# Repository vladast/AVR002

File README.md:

# AVR-based event recorder with USB support

Event recorder device based on AVR processor, with the USB support enabled via V-USB library.

* **Project code name**: Fisherman's Friend
* **Homepage**: https://github.com/vladast/avr-based-event-recorder-with-usb-support

## Hardware

Key components of the hardware implementation are:
* **Atmel's Atmega8 processor**: a heart of the device, within which all logic lies.
* **ST's 24c64 EEPROM**: a persistent memory of the device.

Schematic diagram and PCB outline are created with Eagle v6 and can be found within **hw** directory.

## Software

Software part of the project consist of two parts:
* **Firmware**: a program being uploaded to device.
* **Test application**: a program running on host machine.

Programming languages used: C & C++.

Source code is located within **sw** directory.

## Configuration

There are couple of properties that have to be updated within Makefile before build can be started - following values should be set correctly:
* **PROGRAMMER**: By default, it states *rs232* which is the programmer used on test circuit. It should be set to the programmer's name from avrdude's configuration.
* **USB_CFG_VENDOR_ID**: USB VID 16bit value (see Makefile comments for more info, or refer to V-USB's site)
* **USB_CFG_DEVICE_ID**: USB PID 16bit value (see Makefile comments for more info, or refer to V-USB's site)
* **USB_CFG_VENDOR_NAME**: Name of the vendor. By default, for testing purposes, it's set to "TEST"
* **USB_CFG_VENDOR_NAME_LEN**: Number of chars within your vendor's name. For "TEST" string, that number is 4.
* **USB_CFG_DEVICE_NAME**: Name of your product. By default, for testing purposes, it's set to "TEST"
* **USB_CFG_DEVICE_NAME_LEN**: Number of chars within your vendor's name. For "TEST" string, that number is 4.

## Build procedure

At this moment, Makefile has only been intended for usage on Linux-based build machines with gcc and avr-gcc compilers installed. 
In general, with some modifications, it can be used on other platforms.

To build both firmware and test application run:

```
make build
```

To build only device's firmware (HEX file):

```
make build_hex
```

And to build only test application for host machine:

```
make build_test
```

To list all options from Makefile, run:

```
make
```

## Uploading firmware onto device

Used Makefile is configured for usage of *avrdude* programmer. To upload firmware to AVR located on device run:

```
make burn_firmware
```

**Note**: To use external crystal oscillator, for AVR chip used (which is Atmega8 at this moment), fuses has to be set first. To do so, run:

```
make burn_fuses
```

Of course, both of those commands should be issued as is from **sw** directory.

## 3rd party libraries

Following libraries were used:

* **V-USB**: A firmware-only USB driver for Atmel AVR Microcontrollers, enabling USB communication with host device. Library itself and documentation can be found on www.obdev.at/vusb/. 
V-USB is licensed under GPL version 2.
* **24C EEPROM SPI**: Enables easy SPI communication with external EEPROM. It's usage is well described on http://extremeelectronics.co.in/avr-tutorials/easy-24c-i2c-serial-eeprom-interfacing-with-avr-microcontrollers/

## Author and Licence

**avr-based-event-recorder-with-usb-support** repository is maintained by *Vladimir Stankovic*.

This project is licensed under *GPL Version 2*. Please, refer to LICENSE file for the full text of the license.

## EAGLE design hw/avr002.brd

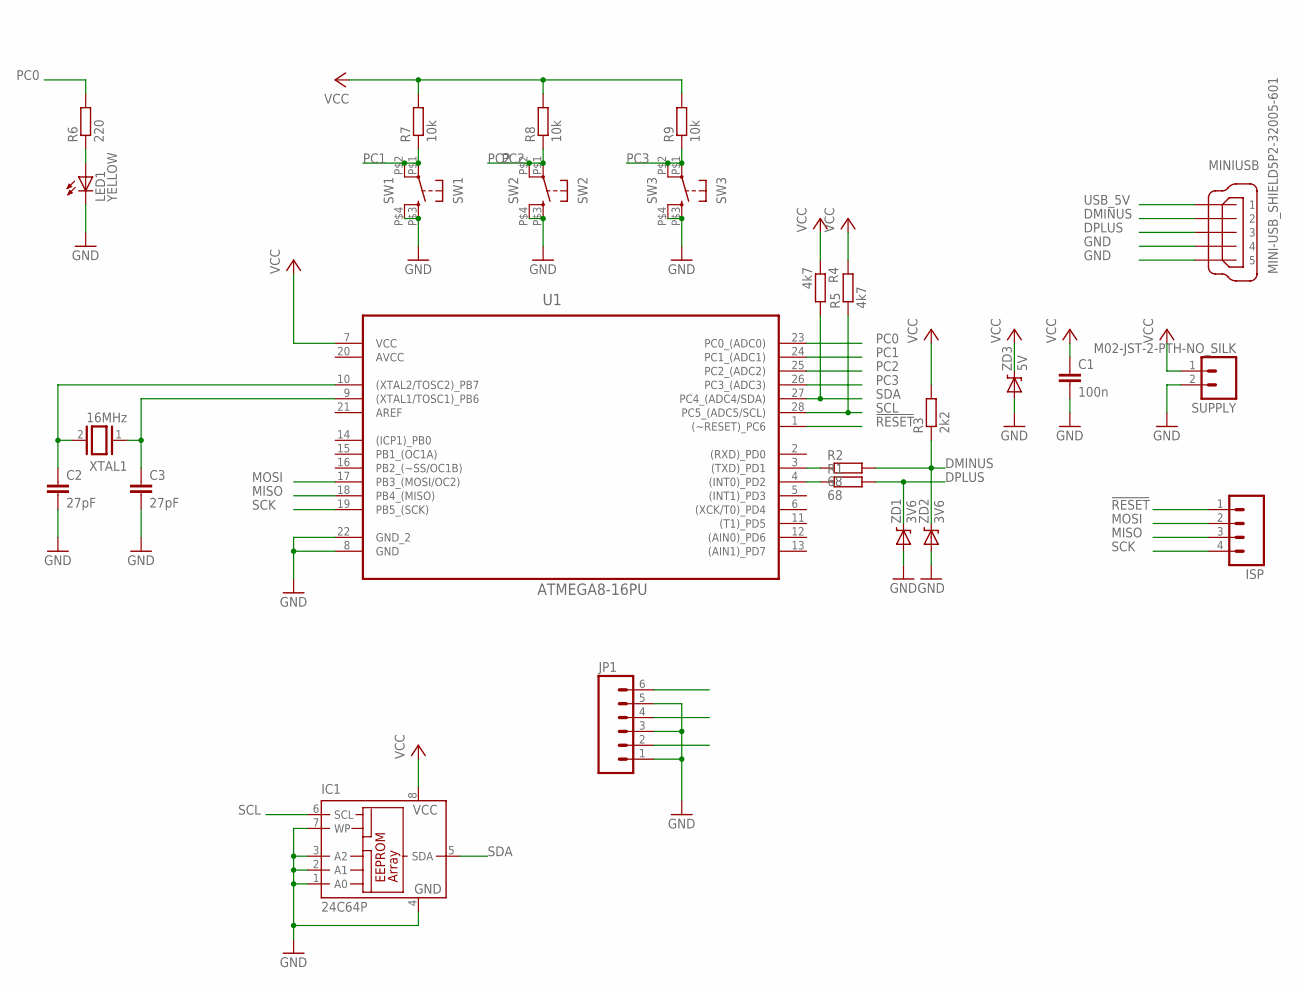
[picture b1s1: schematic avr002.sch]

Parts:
C1: 100n; C050-024X044
C2, C3: 27pF; C050-024X044
IC1: 24C64P; DIL8
ISP: M04POLAR; MOLEX-1X4
JP1: M06POLAR; MOLEX-1X6
LED1: YELLOW; LED5MM
MINIUSB: MINI-USB_SHIELD5P2-32005-601; 32005-601
R1, R2: 68; 0204/7
R3: 2k2; 0204/7
R4, R5: 4k7; 0204/7
R6: 220; 0204/7
R7, R8, R9: 10k; 0204/7
SUPPLY: M02-JST-2-PTH-NO_SILK; JST-2-PTH-NS
SW1: SW1; KSA_SEALED_TAC_SWITCH
SW2: SW2; KSA_SEALED_TAC_SWITCH
SW3: SW3; KSA_SEALED_TAC_SWITCH
U1: ATMEGA8-16PU; DIP254P762X457-28
XTAL1: 16MHz; Q
ZD1, ZD2: 3V6; DIODE-ZENER
ZD3: 5V; DIODE-ZENER

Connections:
!RESET: ISP.1, U1.1 ((~RESET)_PC6)
AVCC: U1.20 (AVCC)
DMINUS: MINIUSB.2, R2.2, R3.1, ZD2.P$1 (C)
DPLUS: MINIUSB.3, R1.2, ZD1.P$1 (C)
GND: C1.2, C2.2, C3.2, IC1.1 (A0), IC1.2 (A1), IC1.3 (A2), IC1.4 (GND), IC1.7 (WP), JP1.1, JP1.3, JP1.5, LED1.K (C), MINIUSB.4, MINIUSB.5, SUPPLY.2, SW1.P$3 (3), SW1.P$4 (4), SW2.P$3 (3), SW2.P$4 (4), SW3.P$3 (3), SW3.P$4 (4), U1.8 (GND), U1.22 (GND_2), ZD1.P$2 (A), ZD2.P$2 (A), ZD3.P$2 (A)
MISO: ISP.3, U1.18 (PB4_(MISO))
MOSI: ISP.2, U1.17 (PB3_(MOSI/OC2))
unnamed: R1.1, U1.4 ((INT0)_PD2)
unnamed: R2.1, U1.3 ((TXD)_PD1)
unnamed: C2.1, U1.10 ((XTAL2/TOSC2)_PB7), XTAL1.2
unnamed: C3.1, U1.9 ((XTAL1/TOSC1)_PB6), XTAL1.1
unnamed: LED1.A, R6.1
PC0: R6.2, U1.23 (PC0_(ADC0))
PC1: JP1.2, R7.1, SW1.P$1 (1), SW1.P$2 (2), U1.24 (PC1_(ADC1))
PC2: JP1.4, R8.1, SW2.P$1 (1), SW2.P$2 (2), U1.25 (PC2_(ADC2))
PC3: JP1.6, R9.1, SW3.P$1 (1), SW3.P$2 (2), U1.26 (PC3_(ADC3))
SCK: ISP.4, U1.19 (PB5_(SCK))
SCL: IC1.6 (SCL), R5.1, U1.28 (PC5_(ADC5/SCL))
SDA: IC1.5 (SDA), R4.2, U1.27 (PC4_(ADC4/SDA))
USB_5V: MINIUSB.1
VCC: C1.1, IC1.8 (VCC), R3.2, R4.1, R5.2, R7.2, R8.2, R9.2, SUPPLY.1, U1.7 (VCC), ZD3.P$1 (C)

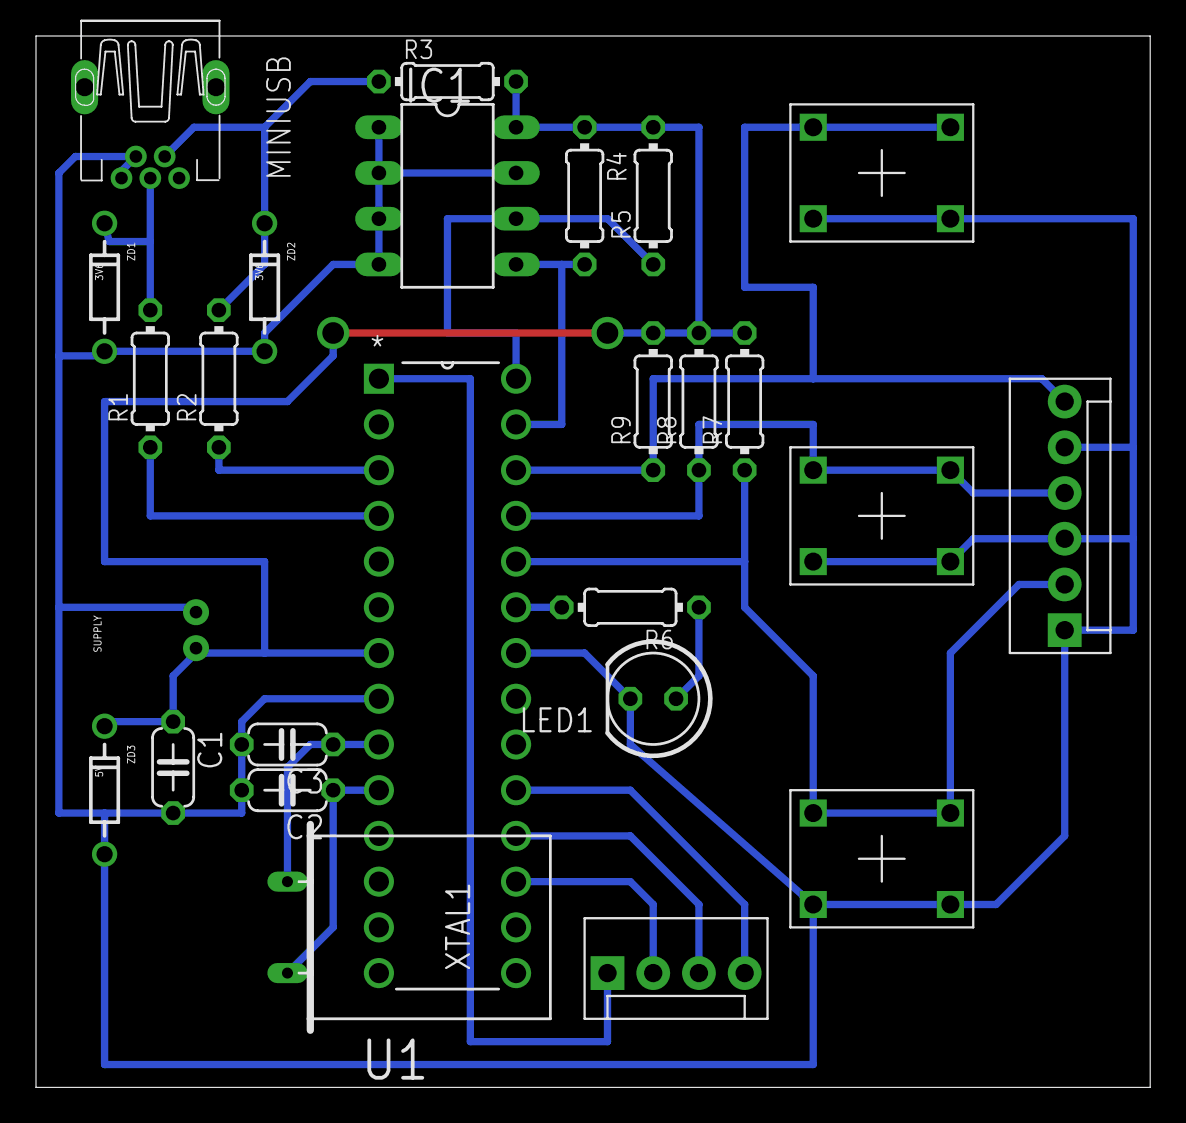
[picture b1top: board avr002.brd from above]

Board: 2 copper layers, 61.9 x 58.4 mm, 26 parts (0 on the bottom side), 19 nets.

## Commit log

2014-03-20 Initial copy from AVR001 project
2014-03-20 removed avr001 files
2014-03-20 Added Qt Creator files
2014-03-20 Commented timer usage from avr001 project and removed oscillator calibration since crystal oscillator is going to be used
2014-03-20 Modified usbFunctionSetup to send SWITCH1 and SWITCH2 states
2014-03-21 Redefined values for atmega8
2014-03-21 Redefined port values used with atmega8
2014-03-21 Redefined F_CPU value to 16MHz
2014-03-21 Enabled USB support back for atmega8
2014-03-21 Added defines for AVR002
2014-03-21 Updated FUSE_L value to 0xEF
2014-03-21 Timer1 interrupt implemented - using comparison instead of overflow
2014-03-21 Removed comments about attiny85 from initTimer()
2014-03-21 Removed unimplemented timer interrupts
2014-03-21 Added AVR315 files for TWI
2014-03-22 Added 24c64 files
2014-03-22 Implemented usage of 24c64 lib
2014-03-22 Removed non-working TWI libs
2014-03-22 Removed TinyWireM object file
2014-03-22 Removed old avr001 files
2014-03-22 Removed binary and object files
2014-03-22 Removed TWI_Master from build
2014-03-22 Removed includes for non-working TWI libs
2014-03-22 Removed usage of excluded TWI library
2014-03-22 Removed unecessary comments from earlier tryouts
2014-03-22 Defined get and set requests
2014-03-22 Reorganized defines
2014-03-23 Added initialization of Timer0 and created interrupt handler for Timer0 overflows
2014-03-23 Implemented switch state detection in Timer0 interrupt
2014-03-23 Fixed USB connect counter logic
2014-03-25 Fixed an issue with invalid request value -> changed value of REQ_GET_HEADER to 0x00
2014-03-25 Set USB_CFG_DEVICE_NAME to appropriate value for AVR002 project
2014-03-26 Passing V-USB vendor/device defines via Makefile
2014-03-26 Implemented processing of REQ_GET_HEADER request
2014-03-26 Implemented structure for USB requests processing and reordered eeprom functions
2014-03-27 Resolved an issue with session counter
2014-03-28 Implemented switch-state detection and signalization + 5secs detection of middle switch state, initiating UPLOAD state
2014-03-28 Implemented temporary fix for session count issue
2014-03-29 Implemented basic write to external EEPROM and processing of REQ_GET_DATA5 requests
2014-03-29 Implemented CNT value storage with overflow logic
2014-03-29 SAMPLING_TIME_WINDOW set to 1, so that events are being detected every second, not every 5 seconds
2014-03-30 Removed old Qt project files from parent directory
2014-03-30 In the case that two touchswitches are pressed at the same time, break the processing of the event
2014-03-30 Updated Qt project files
2014-03-30 Breaking execution when invalid state (two touchshitches pressed) is detected
2014-03-30 Removed unused Wait() function
2014-03-30 Removed most of the outdated comments
2014-03-30 Added Copyright header on top of the file
2014-03-30 Using V-USB USB_CFG_VENDOR_NAME parameter for vendor name
2014-03-30 Removed redefined values that are already used by V-USB and defined DEVICE_CODE value for device distinction purposes
2014-03-30 Updated note about location of License.txt file within project file structure
2014-03-30 Imported from https://vladast:c4291cc689bfc9c448f8eb8b61f5eea63b0cd17f@github.com/vladast/AVR002.git
2014-03-30 [Issue #1] - Transfer to UPLOAD state lasts 10secs instead of 5
2014-03-30 [Issue #2] - First recorded session should be session 1, not session 0
2014-03-30 [Issue #3] - USB connection event should not be recorded
2014-04-01 Initial commit of Eagle files for the hardware
2014-04-05 Fixed and issue with INIT state - re-initiating event counter every time an INIT state is being entered
2014-04-05 Fixed and issue with wrong event code storage - binary shift to left is now donw for 5 places into left, as it should have been
2014-04-10 Moved V-USB files into separate directory
2014-04-10 Changed the usage, project define, added V-USB reference, etc.
2014-04-10 Removed doc directory
2014-04-10 Re-initiated Readme file with new title
2014-04-10 Set structure of the document with data about the project itself and the applied license
2014-04-10 Completed initial draft of README file
2014-04-10 Minor change within '3rd party libraries' section
2014-04-10 Corrected the name of EEPROM vendor
2014-04-10 Create gh-pages branch via GitHub
2014-04-11 Removed Qt Creator project files
2014-04-11 Updated PROJECT value to avr-based-event-recorder-with-usb-suppot
2014-04-11 Uploaded renamed source files
2014-04-11 Removed old source files
2014-04-11 Version 0.0.1
2014-04-11 Removed Qt Project files

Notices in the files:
parts and their libraries:
SparkFun-Connectors: Licensing: CC v3.0 Share-Alike You are welcome to use this library for commercial purposes.
